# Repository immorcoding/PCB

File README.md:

# PCB

用 KiCad 10 做的几块 STM32 板子，以及配套的一套 Python 设计工具。原理图、布局、走线、丝印、DRC 都由脚本从数据文件生成，可以重复构建。

> **实验性项目。** 这些板子主要用来验证设计流程和工具，**都没有打样验证过**，可能有错误。不保证可用，使用后果自负。
>
> **Experimental.** These boards exist to test a design flow and its tools. None has been fabricated or verified; they may contain errors. No warranty of any kind; use at your own risk.

## 板子

| 目录 | 内容 | 层数 | 看点 |
|---|---|---|---|
| [`stm32f411_minsys/`](stm32f411_minsys/) | STM32F411 最小系统板，约 53.6 mm 长，双排针 | 2 | 工具链的第一块板 |
| [`steval_fcu001v2/`](steval_fcu001v2/) | 按 ST 评估板 STEVAL-FCU001V2（小四轴飞控）的原理图重新录入，自己画的 40 × 40 mm 板 | 4 | 整层地、电源层分块 |
| [`stm32h743_sdram/`](stm32h743_sdram/) | STM32H743 BGA（0.65 mm 间距）加 SDRAM | 6 | BGA 扇出、并行总线线序和分组等长、电源层按草图分块；布局和走线做法的范例 |

每块板的目录只放数据：原理图页、`board.toml`、`place.toml`、`silk.toml`、走线描述等；H743 板的设计依据在 [`stm32h743_sdram/SPEC.md`](stm32h743_sdram/SPEC.md)。

## 仓库结构

```
Tools/KiCadDesignTools/   设计工具：原理图生成、布局、总线走线、等长规划、铺铜、检查、构建入口
templates/                新板模板（common 通用、C-bga-065 用于 0.65 mm BGA、demo_board 工具链试验件）
docs/design-rules.md      设计规则的数值，以及和 Altium 规则的对照
docs/rule-profiles/       三套规格档：A 通用、B 0.8 mm BGA、C 0.65 mm 及以下 BGA
docs/shape/               流程和约定：推进流程、规则与原理图、布局、电源与铜皮、走线、收尾
docs/tools.md             KiCad / pcbnew 踩过的坑
```

工具的完整索引见 [`Tools/KiCadDesignTools/README.md`](Tools/KiCadDesignTools/README.md)。

## 使用

需要 KiCad 10（用它自带的 Python，里面有 `pcbnew` 模块）。下面假设 KiCad 装在 `D:\KiCad`，装在别处时设环境变量 `KICAD_BIN` 指向它的 `bin` 目录。命令都在仓库根目录下运行：

```powershell
# 构建一块板的某一步（--dry-run 只打印要执行的命令）
D:\KiCad\bin\python.exe -m Tools.KiCadDesignTools.build stm32h743_sdram <步骤> [--dry-run]

# 从模板新建一块板
D:\KiCad\bin\python.exe -m Tools.KiCadDesignTools.build init <名字>

# 改了工具或规则文件后，跑全部基准测试
D:\KiCad\bin\python.exe -m Tools.KiCadDesignTools.regress
```

DRC、铺铜、渲染这类重活由构建入口排队，一次只跑一个、限四个核、低优先级。建议不要绕过构建入口直接并行调用 `kicad-cli`。

## 协议 / License

Copyright © 2026 Immor

本仓库的原创内容（原理图、PCB、构建脚本、工具代码、文档）采用 [知识共享 署名-非商业性使用-相同方式共享 4.0 国际](https://creativecommons.org/licenses/by-nc-sa/4.0/deed.zh-hans)（CC BY-NC-SA 4.0）协议，全文见 [LICENSE](LICENSE)：

- 可以学习、复制、修改，但必须**署名**并注明来源链接；
- **不得用于商业目的**（包括销售板子或成品，或把设计用在商业产品里）；
- 修改后再发布的作品必须使用**相同协议**。

如需商用授权，请先联系作者。

Original content in this repository (schematics, PCB layouts, build scripts, tool code and documentation) is licensed under [CC BY-NC-SA 4.0](https://creativecommons.org/licenses/by-nc-sa/4.0/). See [LICENSE](LICENSE). For commercial use, contact the author first.

### 例外 / Exceptions

以下第三方内容**不在**上述协议范围内，版权归原作者，按原作者的条款使用：

- `steval_fcu001v2/ref/` 下的 PDF：STMicroelectronics 的文档；
- `steval_fcu001v2/` 的电路（原理图、位号、BOM）：根据 ST 公开的 STEVAL-FCU001V2 资料重新录入，原设计受 ST 的许可条款约束。本仓库只对自己画的 PCB 布局和工具代码授权。

Third-party material listed above is excluded and remains under its owners' terms.

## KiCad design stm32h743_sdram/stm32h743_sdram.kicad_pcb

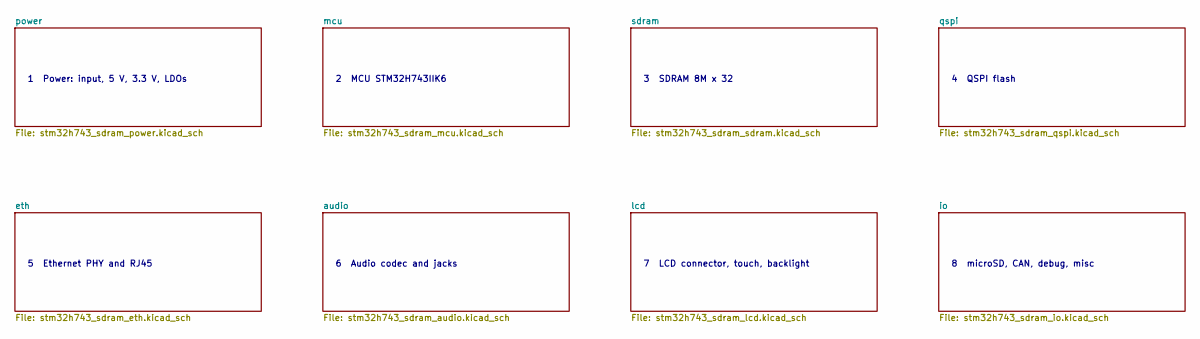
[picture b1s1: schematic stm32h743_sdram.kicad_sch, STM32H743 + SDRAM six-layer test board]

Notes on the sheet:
7 LCD connector, touch, backlight
2 MCU STM32H743IIK6
5 Ethernet PHY and RJ45
4 QSPI flash
3 SDRAM 8M x 32
1 Power: input, 5 V, 3.3 V, LDOs
6 Audio codec and jacks
8 microSD, CAN, debug, misc

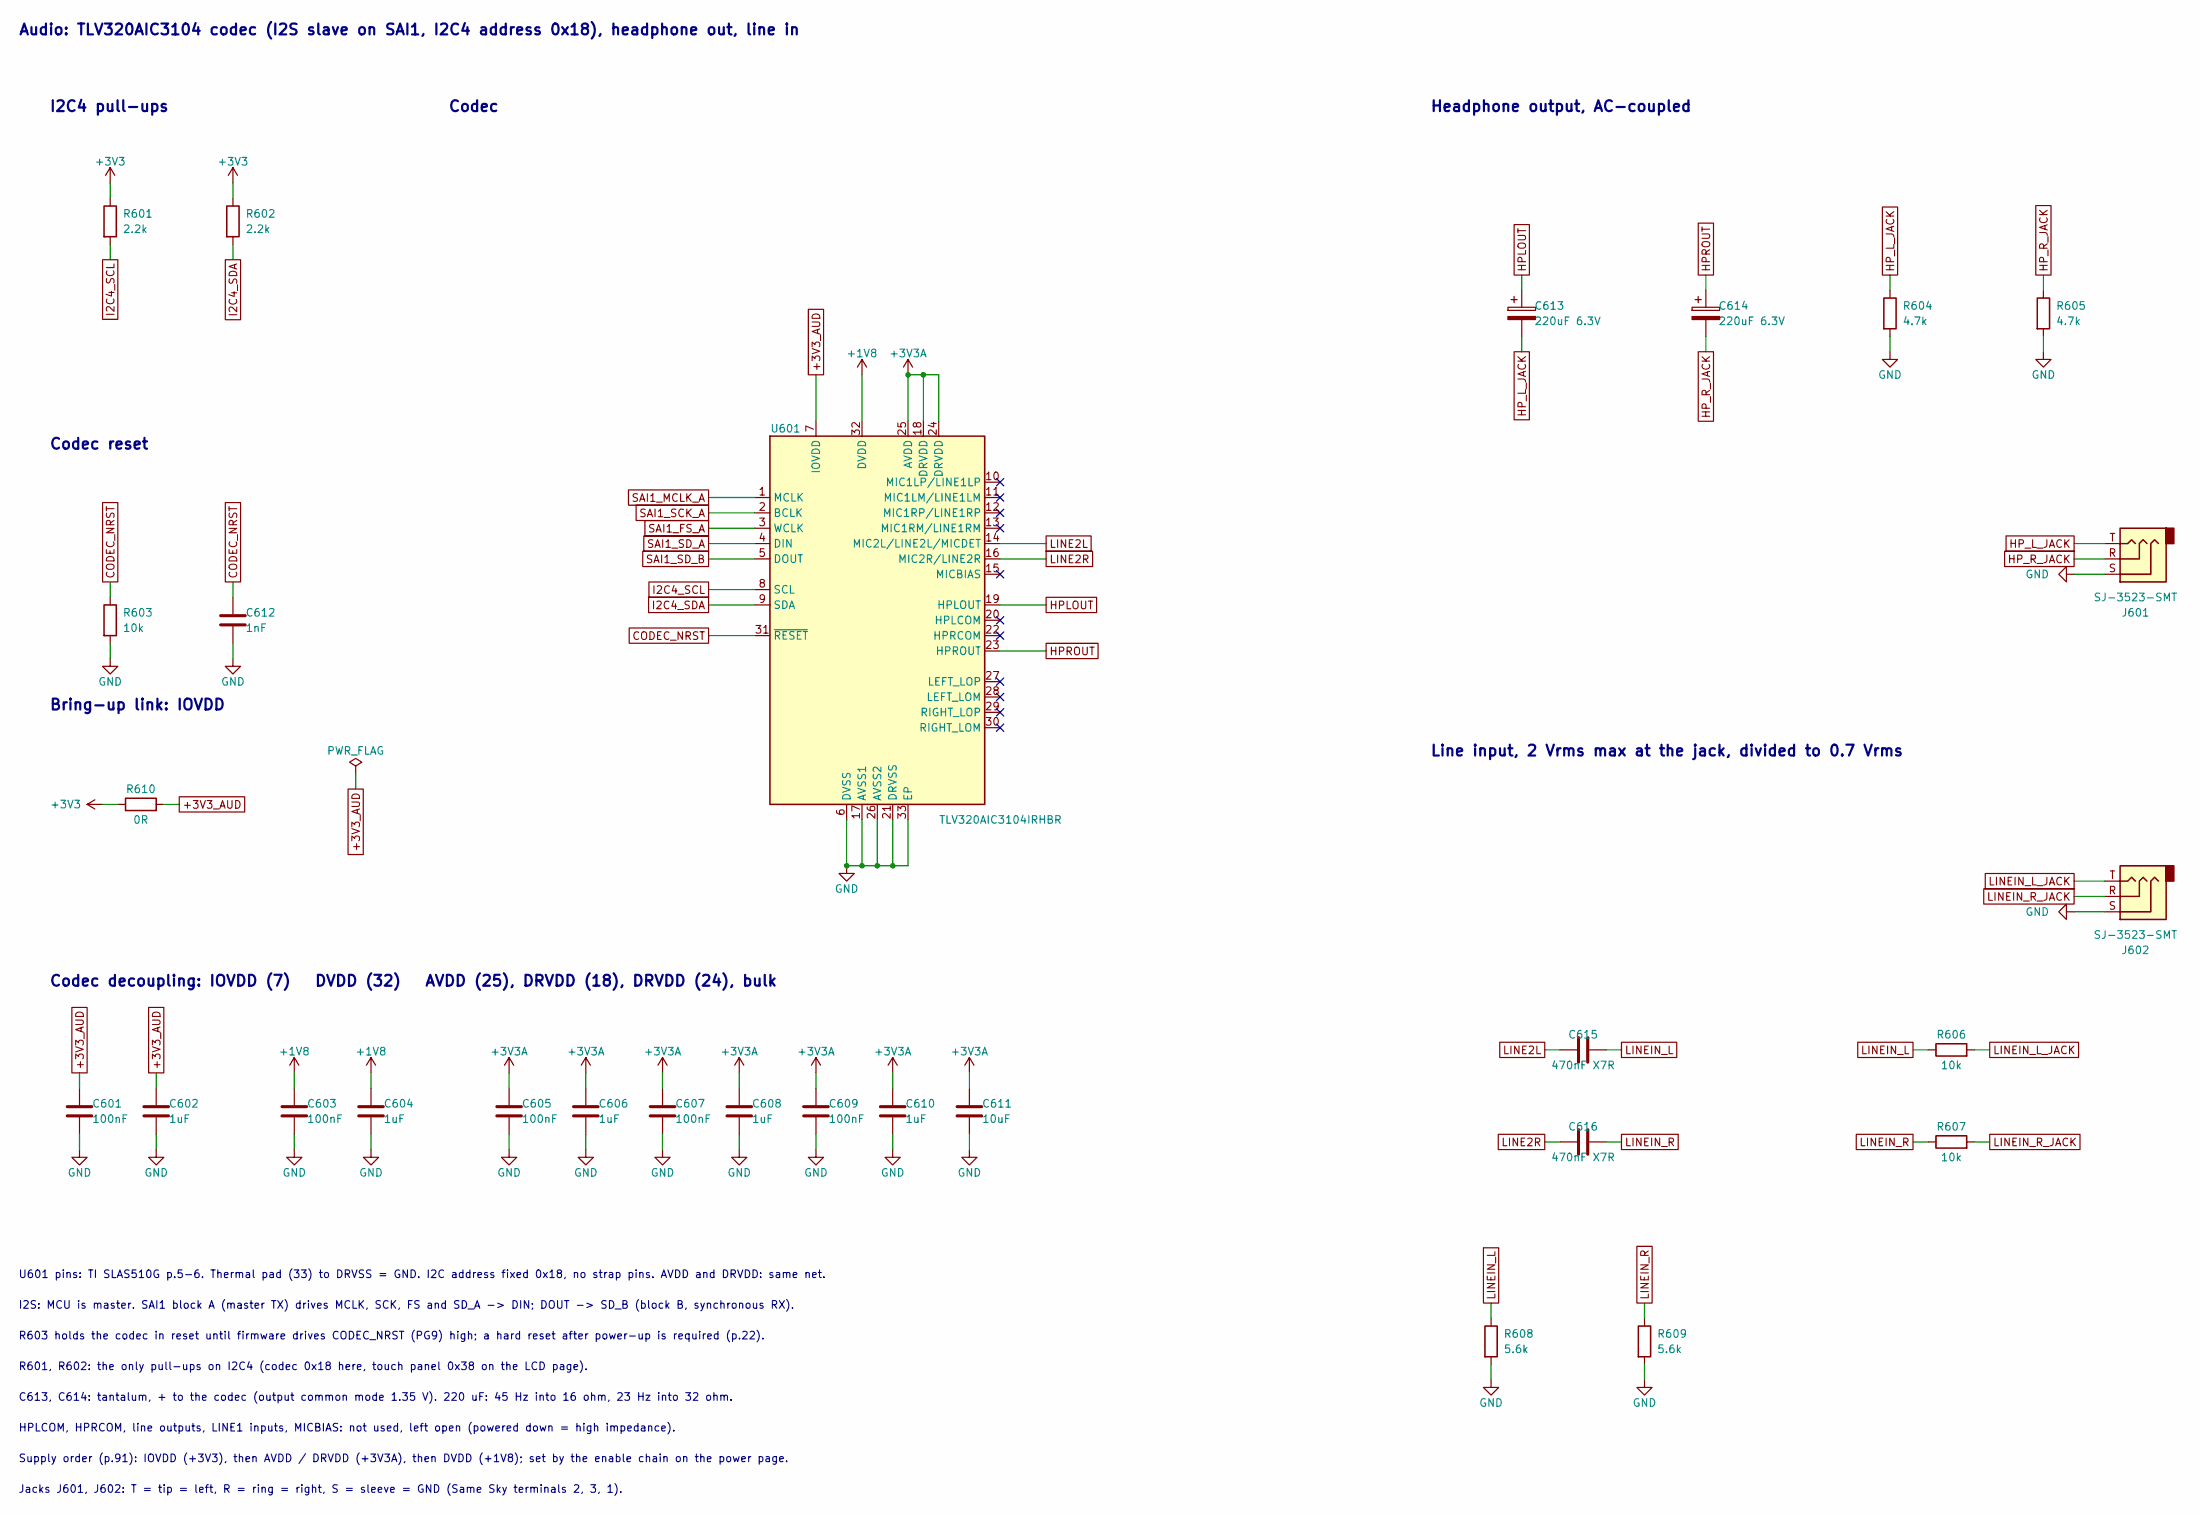
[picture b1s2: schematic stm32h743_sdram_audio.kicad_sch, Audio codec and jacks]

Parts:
C601, C603, C605, C607, C609: 100nF; C_0402_1005Metric
C602, C604, C606, C608, C610: 1uF; C_0603_1608Metric
C611: 10uF; C_0805_2012Metric
C612: 1nF; C_0402_1005Metric
C613, C614: 220uF 6.3V; CP_EIA-7343-31_Kemet-D; MPN 293D227X96R3D2TE3
C615, C616: 470nF X7R; C_0603_1608Metric
J601, J602: SJ-3523-SMT; Jack_3.5mm_CUI_SJ-3523-SMT_Horizontal; MPN SJ-3523-SMT-TR
R601, R602: 2.2k; R_0402_1005Metric
R603, R606, R607: 10k; R_0402_1005Metric
R604, R605: 4.7k; R_0402_1005Metric
R608, R609: 5.6k; R_0402_1005Metric
R610: 0R; R_0603_1608Metric; Rating jumper, 1 A or more
U601: TLV320AIC3104IRHBR; Texas_RHB0032E_VQFN-32-1EP_5x5mm_P0.5mm_EP3.45x3.45mm; MPN TLV320AIC3104IRHBR

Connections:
+1V8: C603.1, C604.1, U601.32 (DVDD); also elsewhere on the board
+3V3: R601.1, R602.1, R610.1; also elsewhere on the board
+3V3A: C605.1, C606.1, C607.1, C608.1, C609.1, C610.1, C611.1, U601.18 (DRVDD), U601.24 (DRVDD), U601.25 (AVDD); also elsewhere on the board
+3V3_AUD: C601.1, C602.1, R610.2, U601.7 (IOVDD)
CODEC_NRST: C612.1, R603.1, U601.31 (~RESET); also elsewhere on the board
GND: C601.2, C602.2, C603.2, C604.2, C605.2, C606.2, C607.2, C608.2, C609.2, C610.2, C611.2, C612.2, J601.S, J602.S, R603.2, R604.2, R605.2, R608.2, R609.2, U601.6 (DVSS), U601.17 (AVSS1), U601.21 (DRVSS), U601.26 (AVSS2), U601.33 (EP); also elsewhere on the board
HPLOUT: C613.1, U601.19 (HPLOUT)
HPROUT: C614.1, U601.23 (HPROUT)
HP_L_JACK: C613.2, J601.T, R604.1
HP_R_JACK: C614.2, J601.R, R605.1
I2C4_SCL: R601.2, U601.8 (SCL); also elsewhere on the board
I2C4_SDA: R602.2, U601.9 (SDA); also elsewhere on the board
LINE2L: C615.1, U601.14 (MIC2L/LINE2L/MICDET)
LINE2R: C616.1, U601.16 (MIC2R/LINE2R)
LINEIN_L: C615.2, R606.1, R608.1
LINEIN_L_JACK: J602.T, R606.2
LINEIN_R: C616.2, R607.1, R609.1
LINEIN_R_JACK: J602.R, R607.2
SAI1_FS_A: U601.3 (WCLK); also elsewhere on the board
SAI1_MCLK_A: U601.1 (MCLK); also elsewhere on the board
SAI1_SCK_A: U601.2 (BCLK); also elsewhere on the board
SAI1_SD_A: U601.4 (DIN); also elsewhere on the board
SAI1_SD_B: U601.5 (DOUT); also elsewhere on the board

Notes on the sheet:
I2C4 pull-ups
Supply order (p.91): IOVDD (+3V3), then AVDD / DRVDD (+3V3A), then DVDD (+1V8); set by the enable chain on the power page.
Codec decoupling: IOVDD (7) DVDD (32) AVDD (25), DRVDD (18), DRVDD (24), bulk
R601, R602: the only pull-ups on I2C4 (codec 0x18 here, touch panel 0x38 on the LCD page).
I2S: MCU is master. SAI1 block A (master TX) drives MCLK, SCK, FS and SD_A -> DIN; DOUT -> SD_B (block B, synchronous RX).
Headphone output, AC-coupled
Codec reset
Line input, 2 Vrms max at the jack, divided to 0.7 Vrms
Bring-up link: IOVDD
R603 holds the codec in reset until firmware drives CODEC_NRST (PG9) high; a hard reset after power-up is required (p.22).
Audio: TLV320AIC3104 codec (I2S slave on SAI1, I2C4 address 0x18), headphone out, line in
Jacks J601, J602: T = tip = left, R = ring = right, S = sleeve = GND (Same Sky terminals 2, 3, 1).
U601 pins: TI SLAS510G p.5-6. Thermal pad (33) to DRVSS = GND. I2C address fixed 0x18, no strap pins. AVDD and DRVDD: same net.
C613, C614: tantalum, + to the codec (output common mode 1.35 V). 220 uF: 45 Hz into 16 ohm, 23 Hz into 32 ohm.
Codec
HPLCOM, HPRCOM, line outputs, LINE1 inputs, MICBIAS: not used, left open (powered down = high impedance).

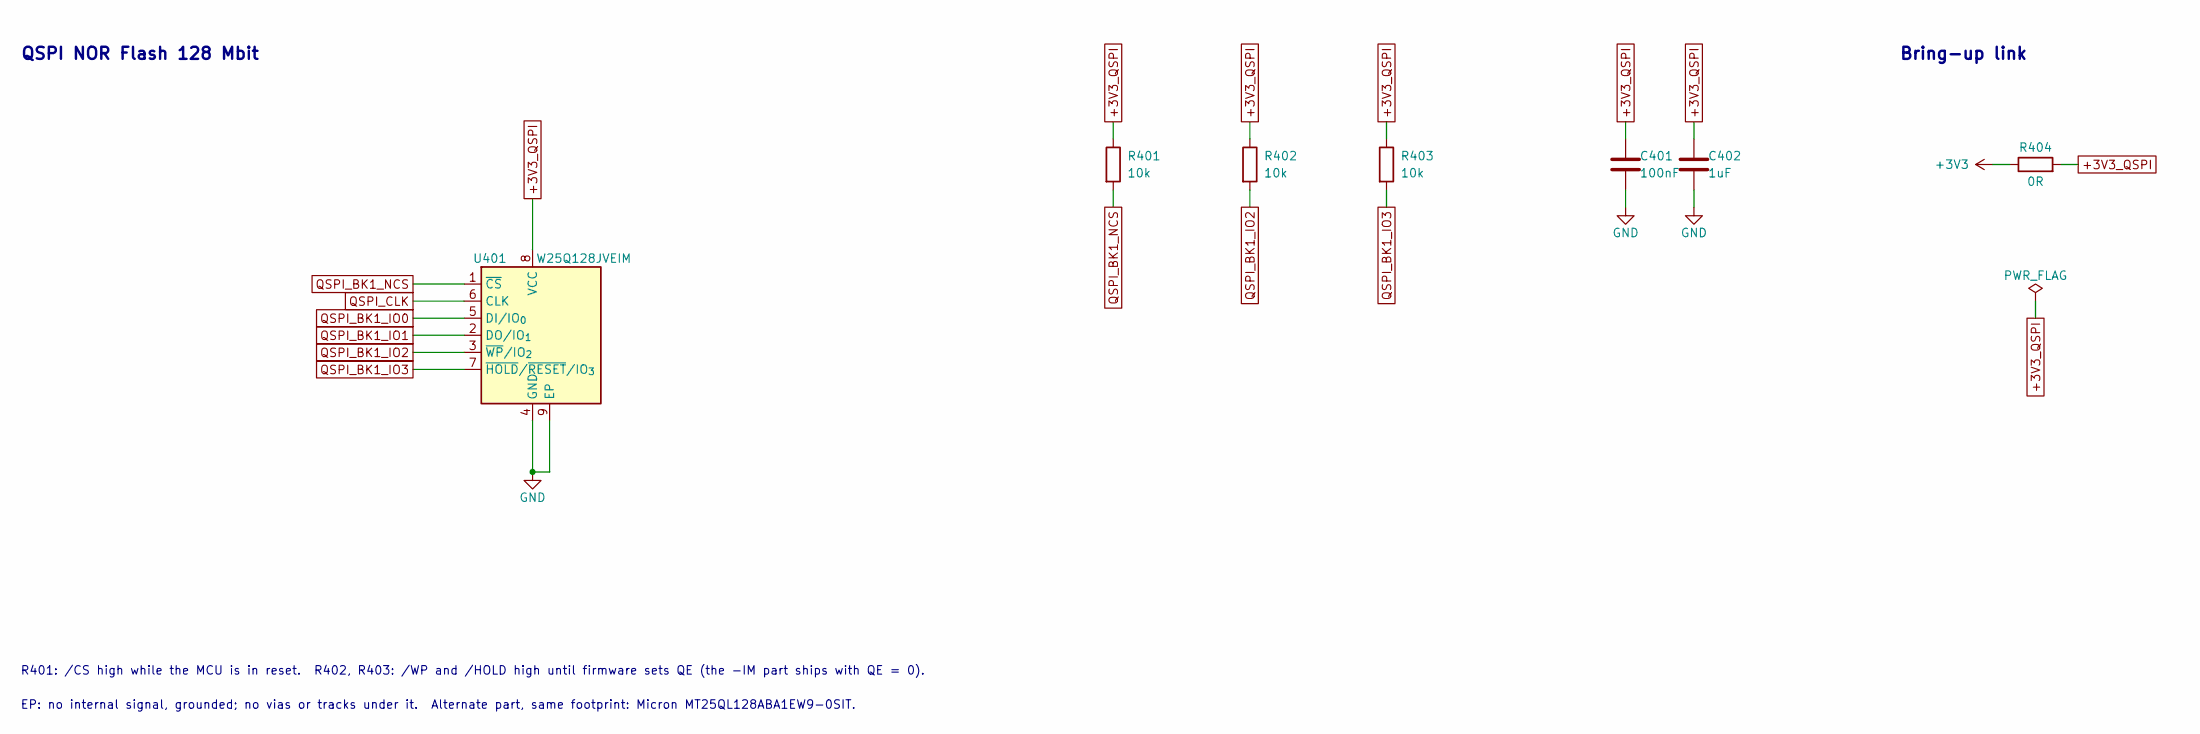
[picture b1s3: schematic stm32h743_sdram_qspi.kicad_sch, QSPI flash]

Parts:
C401: 100nF; C_0402_1005Metric
C402: 1uF; C_0603_1608Metric
R401, R402, R403: 10k; R_0402_1005Metric
R404: 0R; R_0805_2012Metric; Rating jumper, 2 A or more
U401: W25Q128JVEIM; WSON-8-1EP_8x6mm_P1.27mm_EP3.4x4.3mm; MPN W25Q128JVEIM

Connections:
+3V3: R404.1; also elsewhere on the board
+3V3_QSPI: C401.1, C402.1, R401.1, R402.1, R403.1, R404.2, U401.8 (VCC)
GND: C401.2, C402.2, U401.4 (GND), U401.9 (EP); also elsewhere on the board
QSPI_BK1_IO0: U401.5 (DI/IO_{0}); also elsewhere on the board
QSPI_BK1_IO1: U401.2 (DO/IO_{1}); also elsewhere on the board
QSPI_BK1_IO2: R402.2, U401.3 (~WP/IO_{2}); also elsewhere on the board
QSPI_BK1_IO3: R403.2, U401.7 (~HOLD/~RESET/IO_{3}); also elsewhere on the board
QSPI_BK1_NCS: R401.2, U401.1 (~CS); also elsewhere on the board
QSPI_CLK: U401.6 (CLK); also elsewhere on the board

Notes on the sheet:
Bring-up link
R401: /CS high while the MCU is in reset. R402, R403: /WP and /HOLD high until firmware sets QE (the -IM part ships with QE = 0).
QSPI NOR Flash 128 Mbit
EP: no internal signal, grounded; no vias or tracks under it. Alternate part, same footprint: Micron MT25QL128ABA1EW9-0SIT.

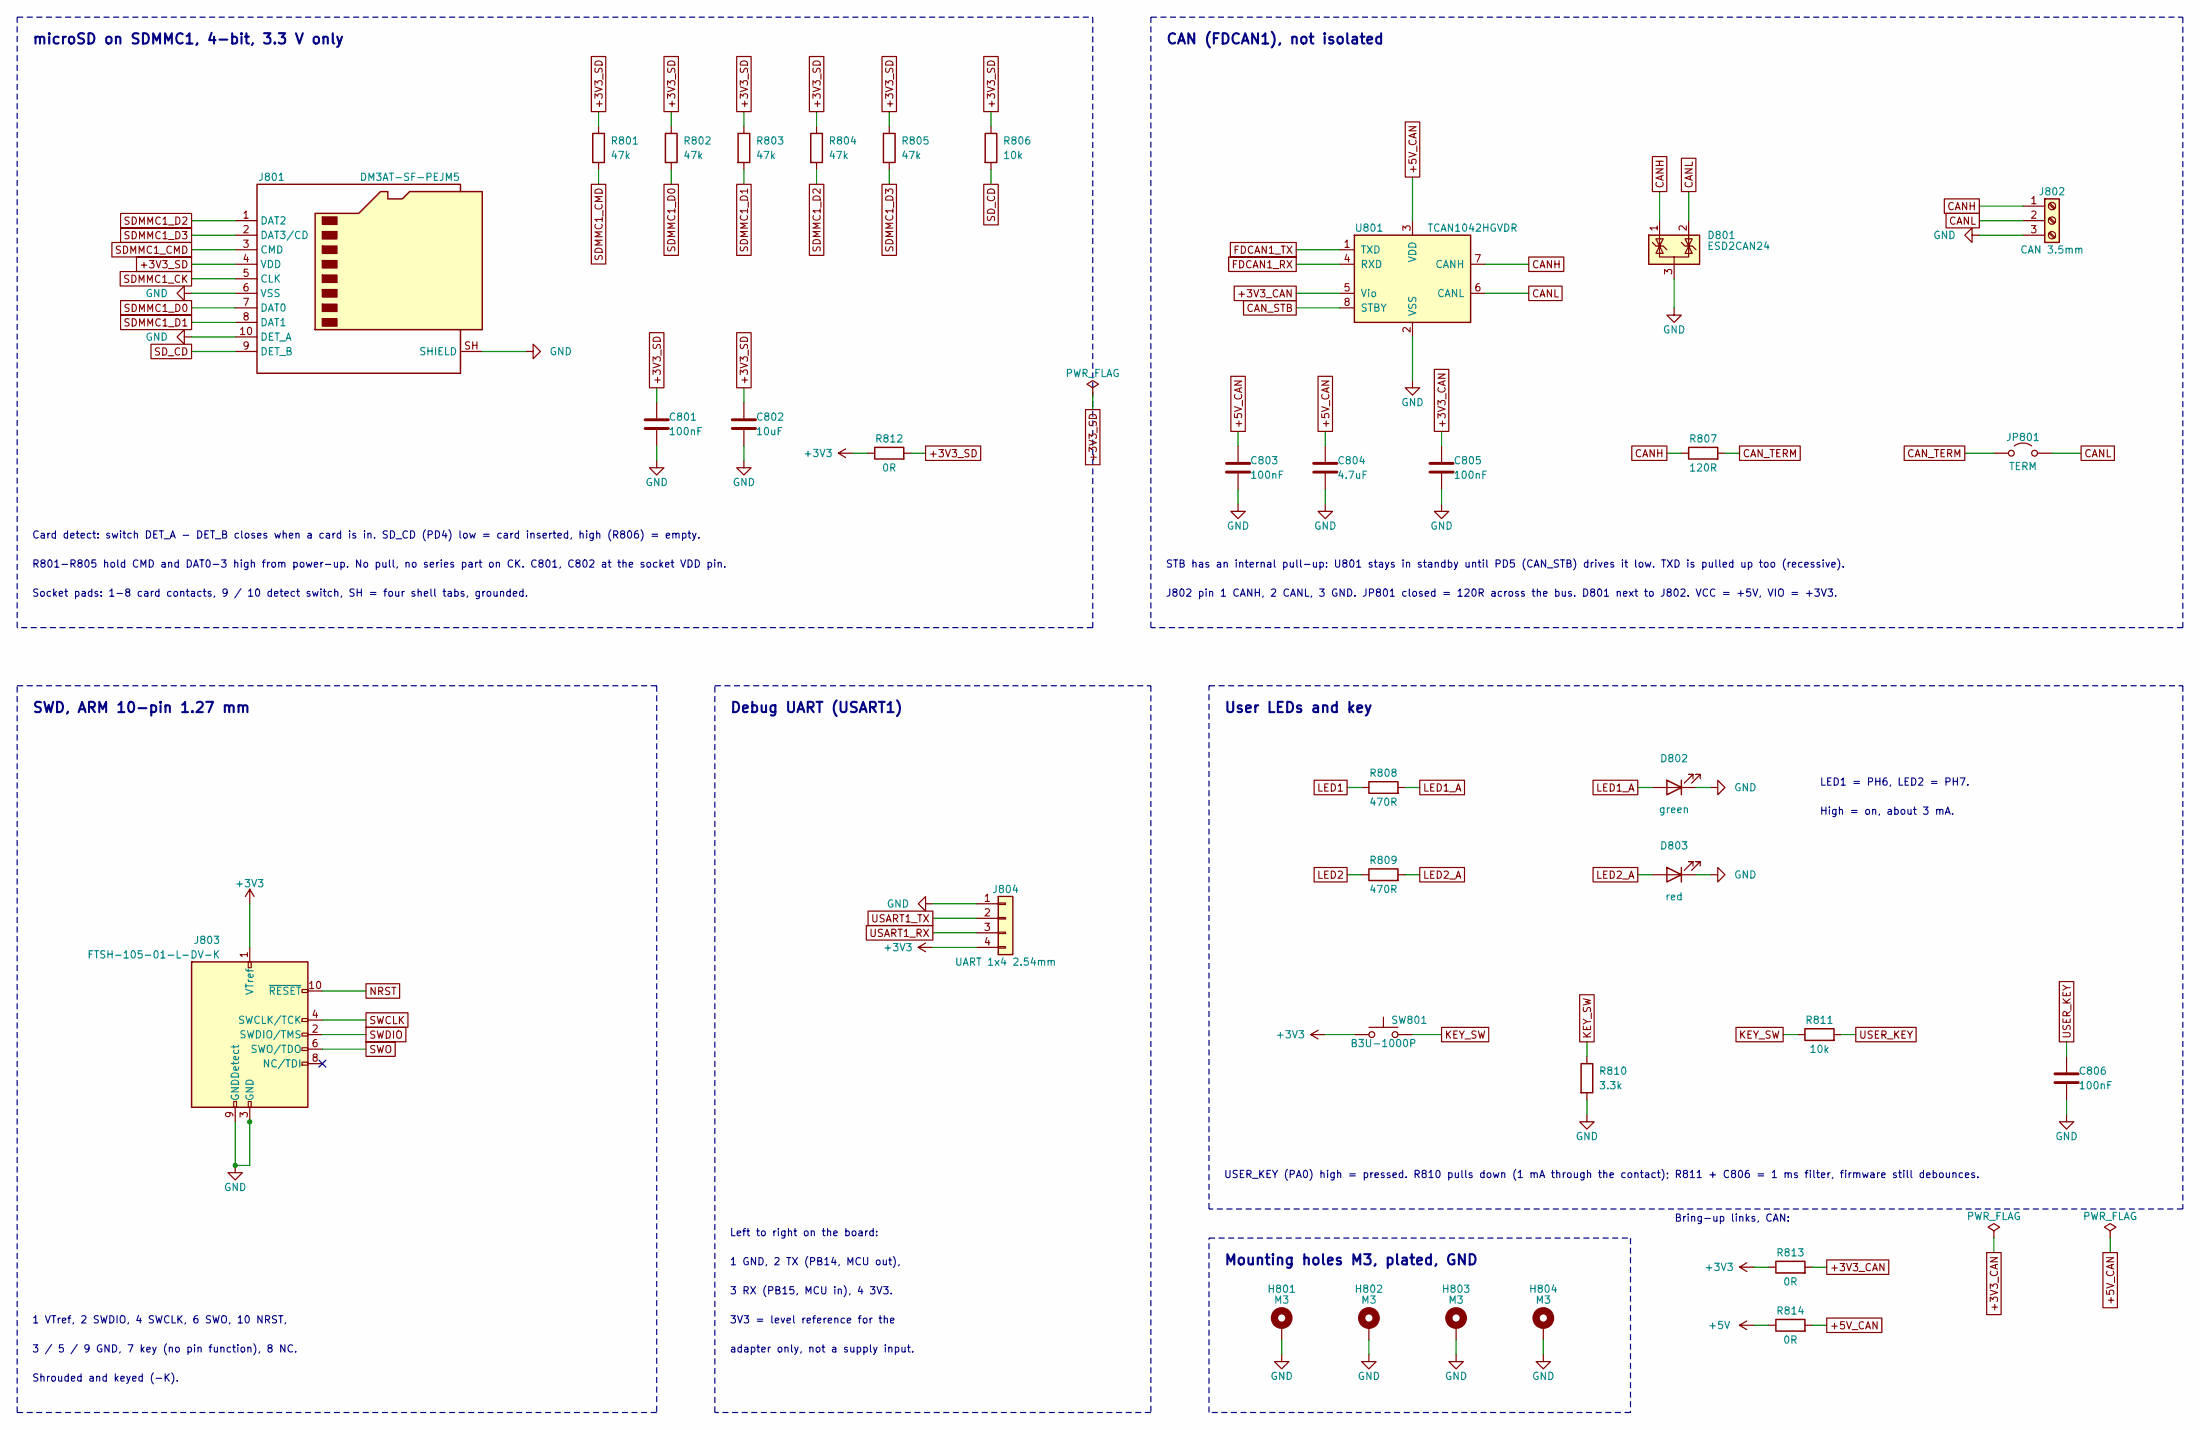
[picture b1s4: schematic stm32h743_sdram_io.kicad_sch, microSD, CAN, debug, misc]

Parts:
C801, C803, C805, C806: 100nF; C_0402_1005Metric
C802: 10uF; C_0805_2012Metric; Rating 10 V X5R or better
C804: 4.7uF; C_0603_1608Metric; Rating 16 V X5R or better
D801: ESD2CAN24; SOT-23; MPN ESD2CAN24DBZRQ1
D802: green; LED_0603_1608Metric; MPN TLMG1100-GS15
D803: red; LED_0603_1608Metric; MPN TLMS1100-GS15
H801, H802, H803, H804: M3; MountingHole_3.2mm_M3_Pad_Via
J801: DM3AT-SF-PEJM5; microSD_HC_Hirose_DM3AT-SF-PEJM5; MPN DM3AT-SF-PEJM5
J802: CAN 3.5mm; TerminalBlock_Phoenix_PT-1,5-3-3.5-H_1x03_P3.50mm_Horizontal; MPN 1984620 (PT 1,5/3-3,5-H)
J803: FTSH-105-01-L-DV-K; PinHeader_2x05_P1.27mm_Vertical_SMD; MPN FTSH-105-01-L-DV-K
J804: UART 1x4 2.54mm; PinHeader_1x04_P2.54mm_Vertical; MPN HTSW-104-07-L-S
JP801: TERM; PinHeader_1x02_P2.54mm_Vertical; MPN HTSW-102-07-L-S
R801, R802, R803, R804, R805: 47k; R_0402_1005Metric
R806, R811: 10k; R_0402_1005Metric
R807: 120R; R_0805_2012Metric; Rating 0805, 1 %, 0.125 W
R808, R809: 470R; R_0402_1005Metric
R810: 3.3k; R_0402_1005Metric
R812, R813, R814: 0R; R_0603_1608Metric; Rating jumper, 1 A or more
SW801: B3U-1000P; SW_SPST_B3U-1000P; MPN B3U-1000P
U801: TCAN1042HGVDR; SOIC-8_3.9x4.9mm_P1.27mm; MPN TCAN1042HGVDR

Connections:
+3V3: J803.1 (VTref), J804.4, R812.1, R813.1, SW801.1; also elsewhere on the board
+3V3_CAN: C805.1, R813.2, U801.5 (Vio)
+3V3_SD: C801.1, C802.1, J801.4 (VDD), R801.1, R802.1, R803.1, R804.1, R805.1, R806.1, R812.2
+5V: R814.1; also elsewhere on the board
+5V_CAN: C803.1, C804.1, R814.2, U801.3 (VDD)
CANH: D801.1 (K), J802.1, R807.1, U801.7 (CANH)
CANL: D801.2 (K), J802.2, JP801.2 (B), U801.6 (CANL)
CAN_STB: U801.8 (STBY); also elsewhere on the board
CAN_TERM: JP801.1 (A), R807.2
FDCAN1_RX: U801.4 (RXD); also elsewhere on the board
FDCAN1_TX: U801.1 (TXD); also elsewhere on the board
GND: C801.2, C802.2, C803.2, C804.2, C805.2, C806.2, D801.3 (A), D802.1 (K), D803.1 (K), H801.1, H802.1, H803.1, H804.1, J801.6 (VSS), J801.10 (DET_A), J801.SH (SHIELD), J802.3, J803.3 (GND), J803.5 (GND), J803.9 (GNDDetect), J804.1, R810.2, U801.2 (VSS); also elsewhere on the board
KEY_SW: R810.1, R811.1, SW801.2
LED1: R808.1; also elsewhere on the board
LED1_A: D802.2 (A), R808.2
LED2: R809.1; also elsewhere on the board
LED2_A: D803.2 (A), R809.2
NRST: J803.10 (~RESET); also elsewhere on the board
SDMMC1_CK: J801.5 (CLK); also elsewhere on the board
SDMMC1_CMD: J801.3 (CMD), R801.2; also elsewhere on the board
SDMMC1_D0: J801.7 (DAT0), R802.2; also elsewhere on the board
SDMMC1_D1: J801.8 (DAT1), R803.2; also elsewhere on the board
SDMMC1_D2: J801.1 (DAT2), R804.2; also elsewhere on the board
SDMMC1_D3: J801.2 (DAT3/CD), R805.2; also elsewhere on the board
SD_CD: J801.9 (DET_B), R806.2; also elsewhere on the board
SWCLK: J803.4 (SWCLK/TCK); also elsewhere on the board
SWDIO: J803.2 (SWDIO/TMS); also elsewhere on the board
SWO: J803.6 (SWO/TDO); also elsewhere on the board
USART1_RX: J804.3; also elsewhere on the board
USART1_TX: J804.2; also elsewhere on the board
USER_KEY: C806.1, R811.2; also elsewhere on the board

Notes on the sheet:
3V3 = level reference for the
Bring-up links, CAN:
adapter only, not a supply input.
1 VTref, 2 SWDIO, 4 SWCLK, 6 SWO, 10 NRST,
3 / 5 / 9 GND, 7 key (no pin function), 8 NC.
R801-R805 hold CMD and DAT0-3 high from power-up. No pull, no series part on CK. C801, C802 at the socket VDD pin.
STB has an internal pull-up: U801 stays in standby until PD5 (CAN_STB) drives it low. TXD is pulled up too (recessive).
Mounting holes M3, plated, GND
Left to right on the board:
Debug UART (USART1)
Socket pads: 1-8 card contacts, 9 / 10 detect switch, SH = four shell tabs, grounded.
1 GND, 2 TX (PB14, MCU out),
microSD on SDMMC1, 4-bit, 3.3 V only
User LEDs and key
USER_KEY (PA0) high = pressed. R810 pulls down (1 mA through the contact); R811 + C806 = 1 ms filter, firmware still debounces.
J802 pin 1 CANH, 2 CANL, 3 GND. JP801 closed = 120R across the bus. D801 next to J802. VCC = +5V, VIO = +3V3.
3 RX (PB15, MCU in), 4 3V3.
Card detect: switch DET_A - DET_B closes when a card is in. SD_CD (PD4) low = card inserted, high (R806) = empty.
High = on, about 3 mA.
CAN (FDCAN1), not isolated
SWD, ARM 10-pin 1.27 mm
LED1 = PH6, LED2 = PH7.
Shrouded and keyed (-K).

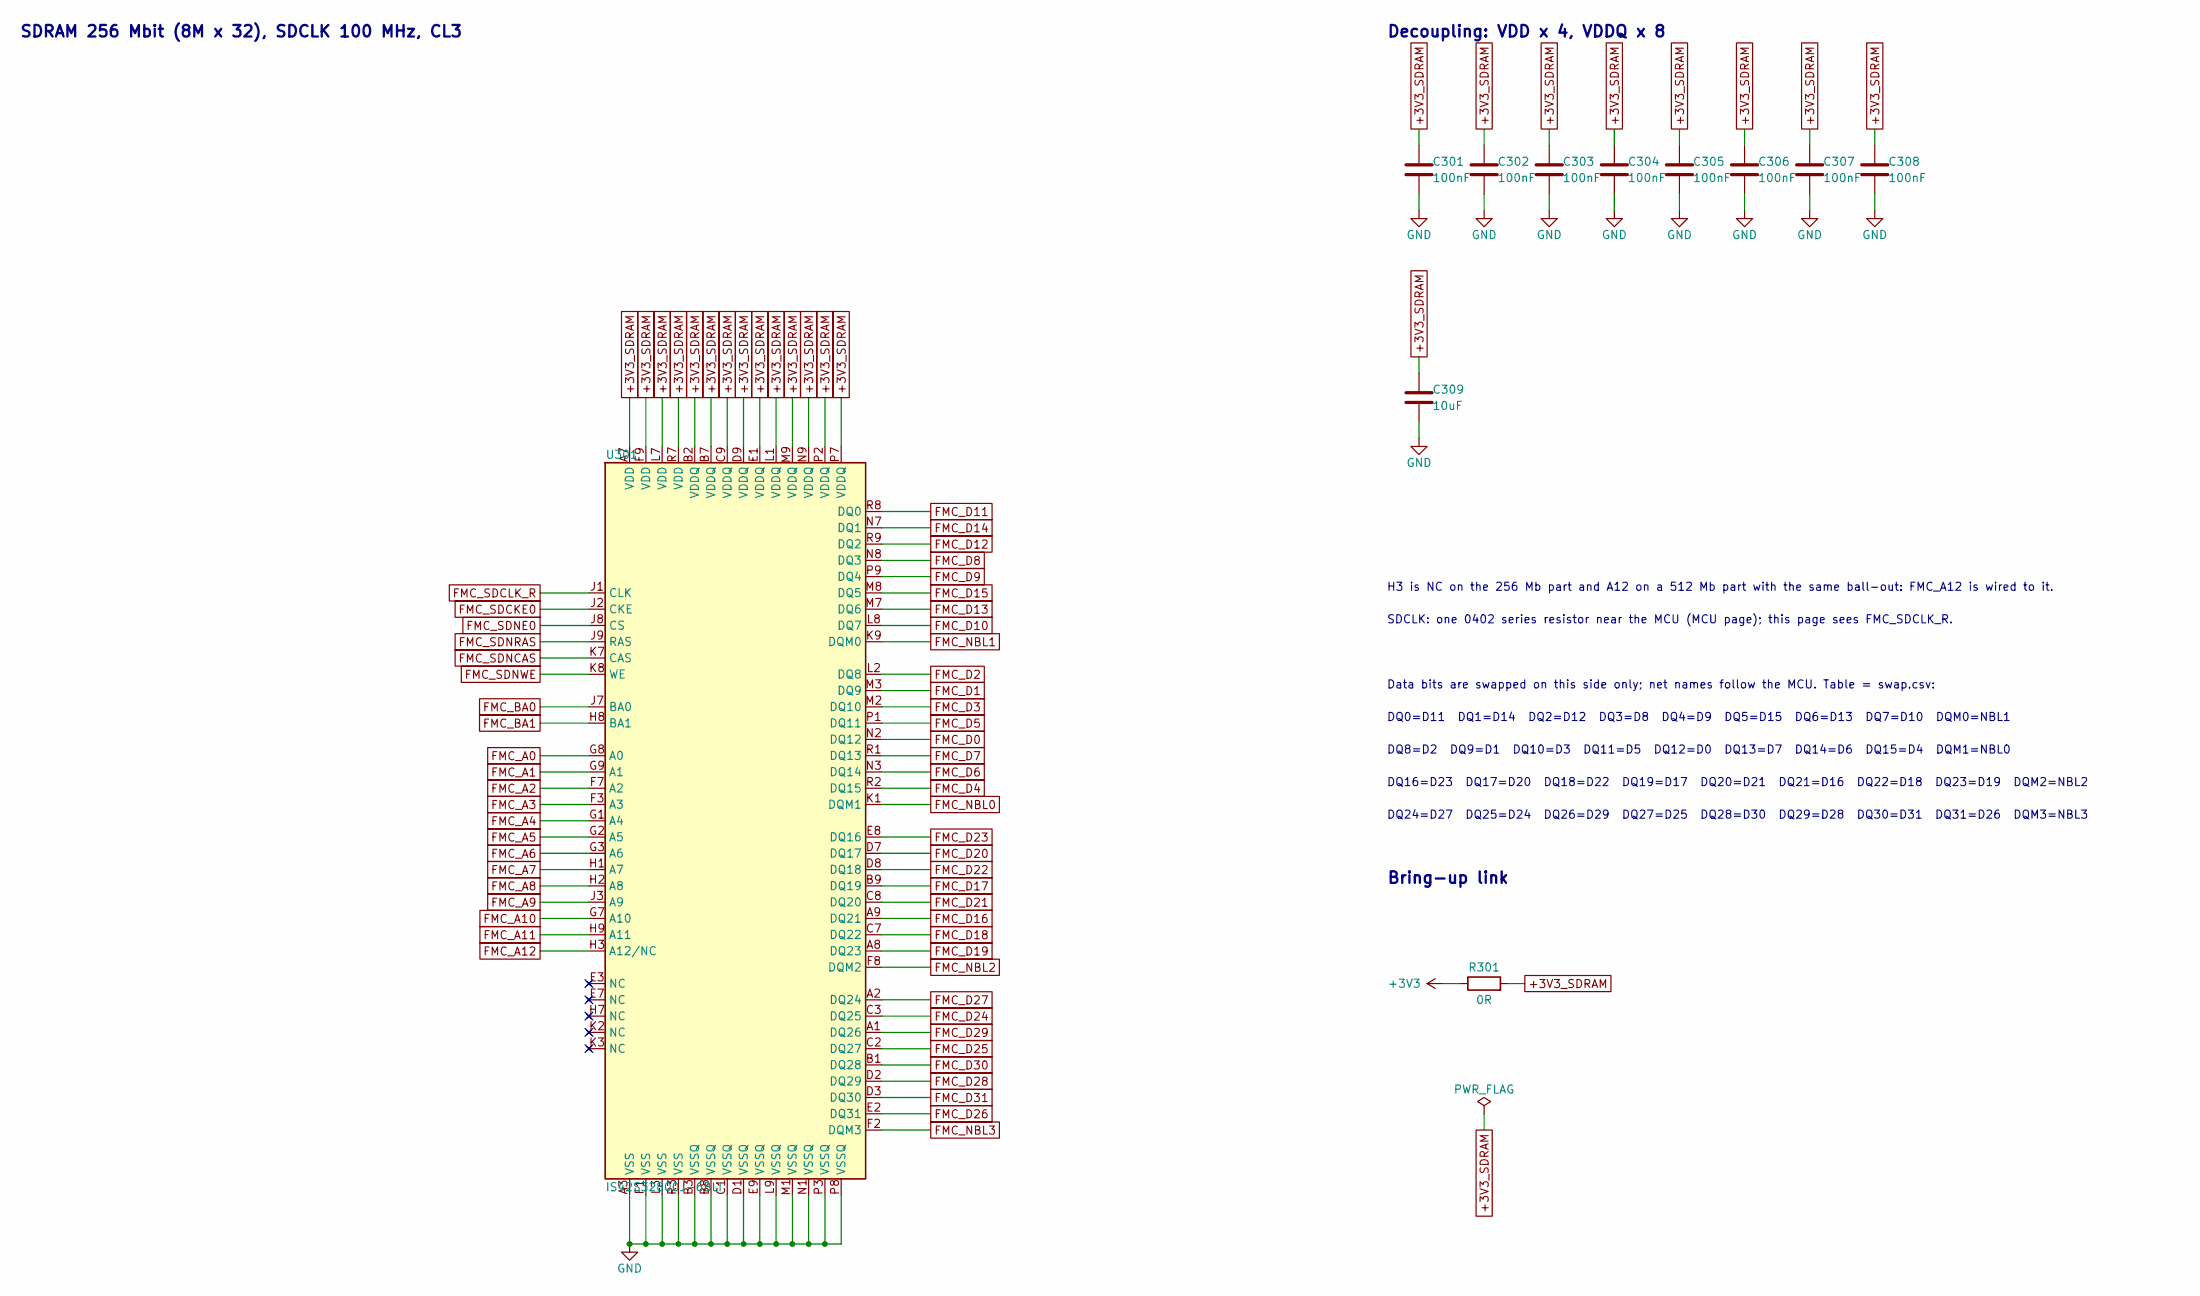
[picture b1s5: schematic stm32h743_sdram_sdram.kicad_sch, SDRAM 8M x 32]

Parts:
C301, C302, C303, C304, C305, C306, C307, C308: 100nF; C_0402_1005Metric
C309: 10uF; C_0805_2012Metric
R301: 0R; R_0805_2012Metric; Rating jumper, 2 A or more
U301: IS42S32800J-6BLI; BGA-90_8.0x13.0mm_Layout2x3x15_P0.8mm_Pad0.33mm; MPN IS42S32800J-6BLI

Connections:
+3V3: R301.1; also elsewhere on the board
+3V3_SDRAM: C301.1, C302.1, C303.1, C304.1, C305.1, C306.1, C307.1, C308.1, C309.1, R301.2, U301.A7 (VDD), U301.B2 (VDDQ), U301.B7 (VDDQ), U301.C9 (VDDQ), U301.D9 (VDDQ), U301.E1 (VDDQ), U301.F9 (VDD), U301.L1 (VDDQ), U301.L7 (VDD), U301.M9 (VDDQ), U301.N9 (VDDQ), U301.P2 (VDDQ), U301.P7 (VDDQ), U301.R7 (VDD)
FMC_A0: U301.G8 (A0); also elsewhere on the board
FMC_A1: U301.G9 (A1); also elsewhere on the board
FMC_A2: U301.F7 (A2); also elsewhere on the board
FMC_A3: U301.F3 (A3); also elsewhere on the board
FMC_A4: U301.G1 (A4); also elsewhere on the board
FMC_A5: U301.G2 (A5); also elsewhere on the board
FMC_A6: U301.G3 (A6); also elsewhere on the board
FMC_A7: U301.H1 (A7); also elsewhere on the board
FMC_A8: U301.H2 (A8); also elsewhere on the board
FMC_A9: U301.J3 (A9); also elsewhere on the board
FMC_A10: U301.G7 (A10); also elsewhere on the board
FMC_A11: U301.H9 (A11); also elsewhere on the board
FMC_A12: U301.H3 (A12/NC); also elsewhere on the board
FMC_BA0: U301.J7 (BA0); also elsewhere on the board
FMC_BA1: U301.H8 (BA1); also elsewhere on the board
FMC_D0: U301.N2 (DQ12); also elsewhere on the board
FMC_D1: U301.M3 (DQ9); also elsewhere on the board
FMC_D2: U301.L2 (DQ8); also elsewhere on the board
FMC_D3: U301.M2 (DQ10); also elsewhere on the board
FMC_D4: U301.R2 (DQ15); also elsewhere on the board
FMC_D5: U301.P1 (DQ11); also elsewhere on the board
FMC_D6: U301.N3 (DQ14); also elsewhere on the board
FMC_D7: U301.R1 (DQ13); also elsewhere on the board
FMC_D8: U301.N8 (DQ3); also elsewhere on the board
FMC_D9: U301.P9 (DQ4); also elsewhere on the board
FMC_D10: U301.L8 (DQ7); also elsewhere on the board
FMC_D11: U301.R8 (DQ0); also elsewhere on the board
FMC_D12: U301.R9 (DQ2); also elsewhere on the board
FMC_D13: U301.M7 (DQ6); also elsewhere on the board
FMC_D14: U301.N7 (DQ1); also elsewhere on the board
FMC_D15: U301.M8 (DQ5); also elsewhere on the board
FMC_D16: U301.A9 (DQ21); also elsewhere on the board
FMC_D17: U301.B9 (DQ19); also elsewhere on the board
FMC_D18: U301.C7 (DQ22); also elsewhere on the board
FMC_D19: U301.A8 (DQ23); also elsewhere on the board
FMC_D20: U301.D7 (DQ17); also elsewhere on the board
FMC_D21: U301.C8 (DQ20); also elsewhere on the board
FMC_D22: U301.D8 (DQ18); also elsewhere on the board
FMC_D23: U301.E8 (DQ16); also elsewhere on the board
FMC_D24: U301.C3 (DQ25); also elsewhere on the board
FMC_D25: U301.C2 (DQ27); also elsewhere on the board
FMC_D26: U301.E2 (DQ31); also elsewhere on the board
FMC_D27: U301.A2 (DQ24); also elsewhere on the board
FMC_D28: U301.D2 (DQ29); also elsewhere on the board
FMC_D29: U301.A1 (DQ26); also elsewhere on the board
FMC_D30: U301.B1 (DQ28); also elsewhere on the board
FMC_D31: U301.D3 (DQ30); also elsewhere on the board
FMC_NBL0: U301.K1 (DQM1); also elsewhere on the board
FMC_NBL1: U301.K9 (DQM0); also elsewhere on the board
FMC_NBL2: U301.F8 (DQM2); also elsewhere on the board
FMC_NBL3: U301.F2 (DQM3); also elsewhere on the board
FMC_SDCKE0: U301.J2 (CKE); also elsewhere on the board
FMC_SDCLK_R: U301.J1 (CLK); also elsewhere on the board
FMC_SDNCAS: U301.K7 (CAS); also elsewhere on the board
FMC_SDNE0: U301.J8 (CS); also elsewhere on the board
FMC_SDNRAS: U301.J9 (RAS); also elsewhere on the board
FMC_SDNWE: U301.K8 (WE); also elsewhere on the board
GND: C301.2, C302.2, C303.2, C304.2, C305.2, C306.2, C307.2, C308.2, C309.2, U301.A3 (VSS), U301.B3 (VSSQ), U301.B8 (VSSQ), U301.C1 (VSSQ), U301.D1 (VSSQ), U301.E9 (VSSQ), U301.F1 (VSS), U301.L3 (VSS), U301.L9 (VSSQ), U301.M1 (VSSQ), U301.N1 (VSSQ), U301.P3 (VSSQ), U301.P8 (VSSQ), U301.R3 (VSS); also elsewhere on the board

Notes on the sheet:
SDCLK: one 0402 series resistor near the MCU (MCU page); this page sees FMC_SDCLK_R.
SDRAM 256 Mbit (8M x 32), SDCLK 100 MHz, CL3
Bring-up link
DQ24=D27 DQ25=D24 DQ26=D29 DQ27=D25 DQ28=D30 DQ29=D28 DQ30=D31 DQ31=D26 DQM3=NBL3
DQ8=D2 DQ9=D1 DQ10=D3 DQ11=D5 DQ12=D0 DQ13=D7 DQ14=D6 DQ15=D4 DQM1=NBL0
DQ16=D23 DQ17=D20 DQ18=D22 DQ19=D17 DQ20=D21 DQ21=D16 DQ22=D18 DQ23=D19 DQM2=NBL2
Decoupling: VDD x 4, VDDQ x 8
Data bits are swapped on this side only; net names follow the MCU. Table = swap.csv:
DQ0=D11 DQ1=D14 DQ2=D12 DQ3=D8 DQ4=D9 DQ5=D15 DQ6=D13 DQ7=D10 DQM0=NBL1
H3 is NC on the 256 Mb part and A12 on a 512 Mb part with the same ball-out: FMC_A12 is wired to it.
